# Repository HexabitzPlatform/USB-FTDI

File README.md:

# USB-FTDI
Hexabitz 3.3V/0.5A USB to FTDI Cable Circuit Hardware Design

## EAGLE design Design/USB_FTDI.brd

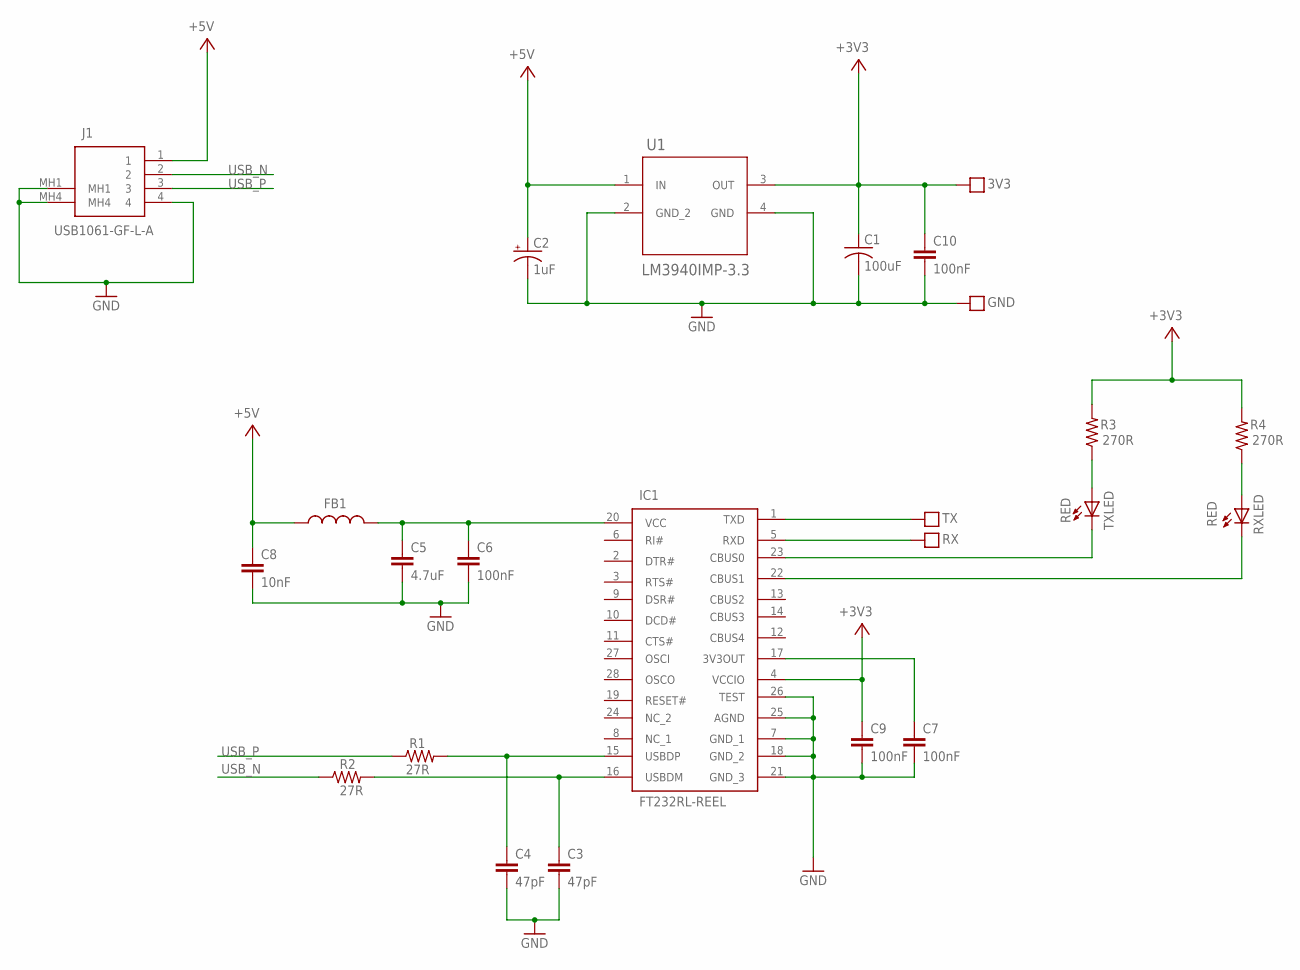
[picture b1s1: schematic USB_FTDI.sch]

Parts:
3V3: PAD5
C1: 100uF; C-1210
C2: 1uF; C-0805-POL
C3, C4: 47pF; C-0603
C5: 4.7uF; C-0805
C6, C7, C9, C10: 100nF; C-0603
C8: 10nF; C-0603
FB1: FB-0603
GND: PAD5
IC1: FT232RL-REEL; SOP65P778X200-28N
J1: USB1061-GF-L-A; USB1061GFLA
R1, R2: 27R; R-0603
R3, R4: 270R; R-0603
RX: PAD5
RXLED: RED; VLMS1300-GS08
TX: PAD5
TXLED: RED; VLMS1300-GS08
U1: LM3940IMP-3.3; SOT230P696X180-4N

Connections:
+3V3: 3V3.P$1, 3V3.P$2, C1.1, C9.1, C10.1, IC1.4 (VCCIO), R3.2, R4.2, U1.3 (OUT)
+5V: C2.1 (+), C8.1, FB1.1, J1.1, U1.1 (IN)
GND: C1.2, C2.2 (-), C3.2, C4.2, C5.2, C6.2, C7.2, C8.2, C9.2, C10.2, GND.P$1, GND.P$2, IC1.7 (GND_1), IC1.18 (GND_2), IC1.21 (GND_3), IC1.25 (AGND), IC1.26 (TEST), J1.4, J1.MH1, J1.MH4, U1.2 (GND_2), U1.4 (GND)
unnamed: R4.1, RXLED.A
unnamed: R3.1, TXLED.A
unnamed: IC1.1 (TXD), TX.P$1, TX.P$2
unnamed: IC1.5 (RXD), RX.P$1, RX.P$2
unnamed: C5.1, C6.1, FB1.2, IC1.20 (VCC)
unnamed: IC1.23 (CBUS0), TXLED.C
unnamed: IC1.22 (CBUS1), RXLED.C
unnamed: C7.1, IC1.17 (3V3OUT)
USBF_N: C3.1, IC1.16 (USBDM), R2.2
USBF_P: C4.1, IC1.15 (USBDP), R1.2
USB_N: J1.2, R2.1
USB_P: J1.3, R1.1

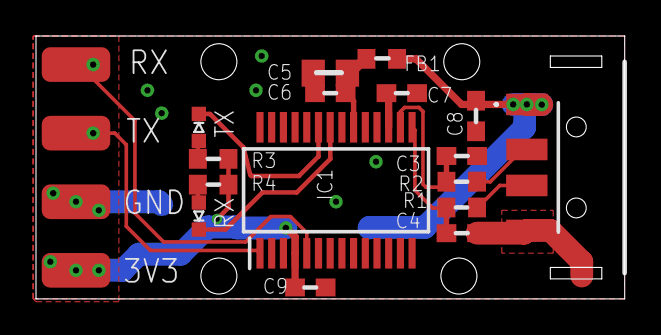
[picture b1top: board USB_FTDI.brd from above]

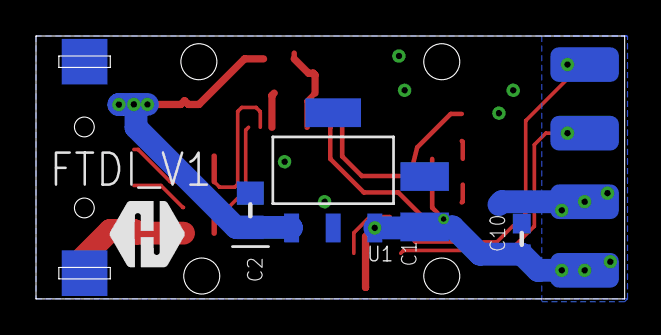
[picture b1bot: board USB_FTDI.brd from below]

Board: 2 copper layers, 32.7 x 14.6 mm, 25 parts (5 on the bottom side), 15 nets.

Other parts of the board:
TRIMBLE-LOGO1: HEXA-LOGO

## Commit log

2024-07-20 Add the V0 files
2024-09-01 - Connect the VCCIO pin of the FTDI IC to the 3.3V - Improve the layout to offer better thermal conductivity for the LDO
